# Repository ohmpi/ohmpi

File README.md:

# OhmPi

Development of a low-cost multi-electrodes resistivity meter for electrical resistivity mesaurement for lab applications, based on raspberry board.

Join the community on [Discord](https://discord.gg/2SCKQZBzXh) to share your experience and provide feedback or use the gitlab issue.

## Installation

1. Download a .zip of this repository (or use `git clone https://gitlab.com/ohmpi/ohmpi.git`)
2. Enter the repository (`cd path/to/ohmpi`) and install the software needed. We made a simple script to make it simpler:

`./install.sh`

The installation script will create a virtual python environement `ohmpy` (with a 'y' at the end) where all packages specified in *requirements.txt* will be installed. The script also takes care of creating a configuration for your hardware if you wish.

To activate the environment and set the necessary `$PYTHONPATH` variable, you can use:

`source env.sh`

More examples are provided in the **[documentation](https://ohmpi.gitlab.io/ohmpi/)**.

## Gallery

A few pictures of the components of the OhmPi. More in the [**DOCUMENTATION**](https://ohmpi.gitlab.io/ohmpi/)!

*Measurement board (v2024).*

*Multiplexer board (v2024).*

*Software architecture.*

## How to contribute

You can contribute to the code of OhmPi directly in this repository by raising issue or making merge request. We use different branches to manage different readiness level of the code:
- `issue_XXX` (e.g. `issue_240`) is a branch linked to an issue number to develop a new feature or fix a bug.
- `alpha`: experimental version of the code to be tested by core developers, this branch contains the latest changes but is **unstable**.
- `beta`: **testing** version, more stable than `alpha` that can be tried out by contributors to provide feedback to core developpers (released in winter). 
- `rc`: **release candidate** branch, version to be extensively tested before being released and merged into the `master` branch (released in spring).
- `master`: more **stable** version of the code. Bug fixes can be merged directly to master.

You can also contribute to the **documentation** (on the `docs` branch) by improving the documentation or showcasing your OhmPi application.

## Citing Ohmpi

If you use OhmPi for you work, please cite [this paper](https://www.sciencedirect.com/science/article/pii/S2468067220300316) as:

    Rémi Clement, Yannick Fargier, Vivien Dubois, Julien Gance, Emile Gros, Nicolas Forquet, OhmPi: An open source data logger for 
    dedicated applications of electrical resistivity imaging at the small and laboratory scale, HardwareX, Volume 8, 2020, e00122, ISSN 2468-0672, https://doi.org/10.1016/j.ohx.2020.e00122..

## License information

You may redistribute and modify this documentation and make products using it under the terms of the CERN-OHL-P v2 (https://cern.ch/cern-ohl). This documentation is distributed WITHOUT ANY EXPRESS OR IMPLIED WARRANTY, INCLUDING OF MERCHANTABILITY, SATISFACTORY QUALITY AND FITNESS FOR A PARTICULAR PURPOSE. Please see the CERN-OHL-P v2 for applicable conditions

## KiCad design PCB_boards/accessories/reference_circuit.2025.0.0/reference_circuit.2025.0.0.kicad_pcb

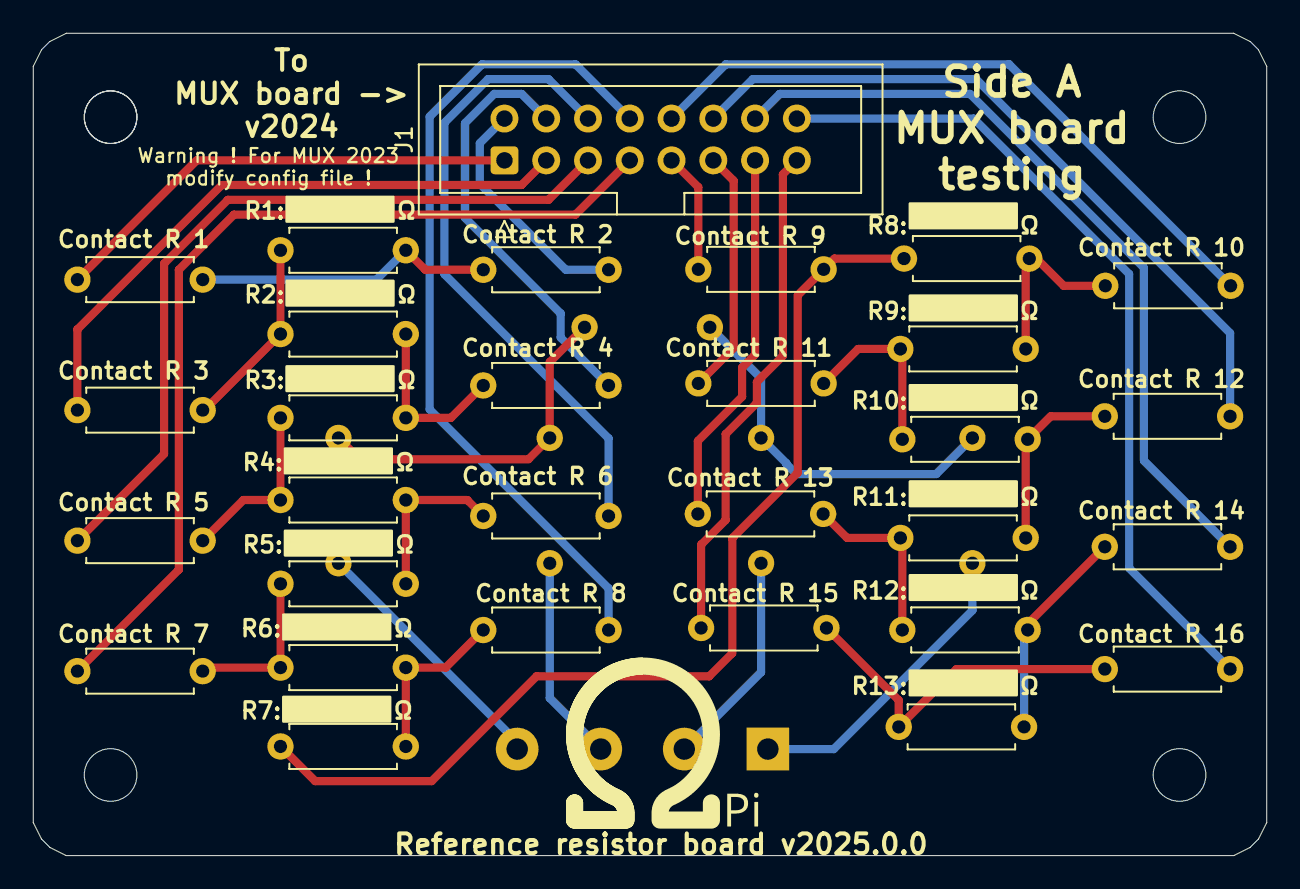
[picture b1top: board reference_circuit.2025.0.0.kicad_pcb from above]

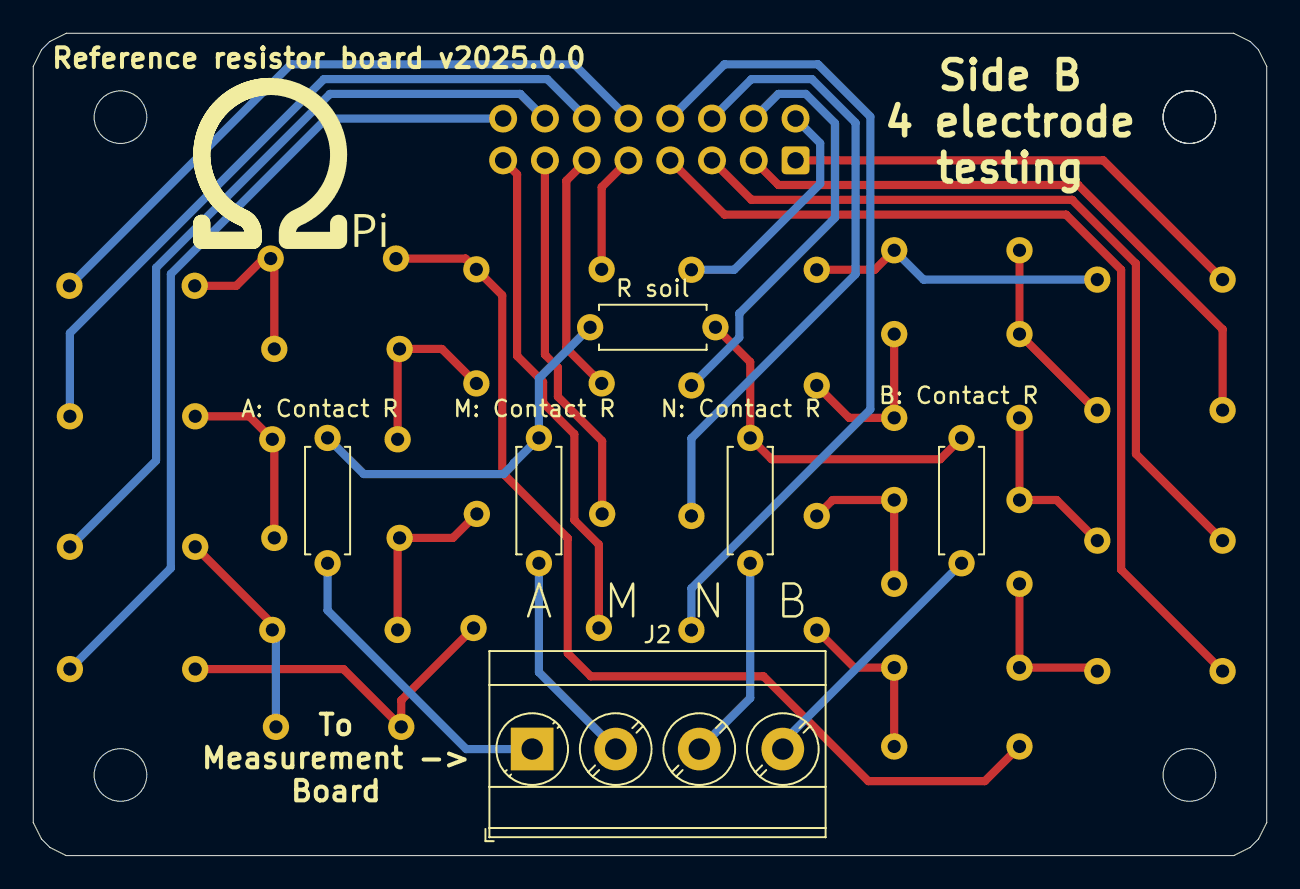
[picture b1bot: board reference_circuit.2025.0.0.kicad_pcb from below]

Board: 2 copper layers, 75.0 x 50.0 mm, 36 parts (6 on the bottom side), 36 nets.

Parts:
A: Contact R: R; R_Axial_DIN0207_L6.3mm_D2.5mm_P7.62mm_Horizontal
B: Contact R: R; R_Axial_DIN0207_L6.3mm_D2.5mm_P7.62mm_Horizontal
J1: Conn_02x08_Odd_Even; IDC-Header_2x08_P2.54mm_Vertical
J2: Screw_Terminal_01x04; TerminalBlock_Phoenix_MKDS-3-4-5.08_1x04_P5.08mm_Horizontal
M: Contact R: R; R_Axial_DIN0207_L6.3mm_D2.5mm_P7.62mm_Horizontal
N: Contact R: R; R_Axial_DIN0207_L6.3mm_D2.5mm_P7.62mm_Horizontal
R1, R2, R3, R4, R5, R6, R7, R8, R9, R10, R11, R12, R13, R14, R15, R16, R18, R19, R20, R21, R22, R23, R24, R25, R26, R27, R28, R29, R30: R; R_Axial_DIN0207_L6.3mm_D2.5mm_P7.62mm_Horizontal
R soil: R; R_Axial_DIN0207_L6.3mm_D2.5mm_P7.62mm_Horizontal

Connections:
unnamed: J1.1, R1.1
unnamed: J1.2, R2.1
unnamed: J1.3, R3.1
unnamed: J1.4, R4.1
unnamed: J1.5, R5.1
unnamed: J1.6, R6.1
unnamed: J1.7, R7.1
unnamed: J1.8, R8.1
unnamed: J1.9, R9.1
unnamed: J1.10, R10.1
unnamed: J1.11, R11.1
unnamed: J1.12, R12.1
unnamed: J1.13, R13.1
unnamed: J1.14, R14.1
unnamed: J1.15, R15.1
unnamed: J1.16, R16.1
unnamed: A: Contact R.1, J2.1
unnamed: J2.2, M: Contact R.1
unnamed: J2.3, N: Contact R.1
unnamed: B: Contact R.1, J2.4
unnamed: R1.2, R2.2, R18.1
unnamed: R10.2, R25.2, R26.1
unnamed: R11.2, R26.2, R27.1
unnamed: R12.2, R27.2, R28.1
unnamed: R13.2, R28.2, R29.1
unnamed: R14.2, R29.2, R30.1
unnamed: R15.2, R16.2, R30.2
unnamed: R3.2, R18.2, R19.1
unnamed: R4.2, R19.2, R20.1
unnamed: R5.2, R20.2, R21.1
unnamed: R6.2, R21.2, R22.1
unnamed: R7.2, R22.2, R23.1
unnamed: R8.2, R23.2, R24.1
unnamed: R9.2, R24.2, R25.1
unnamed: A: Contact R.2, M: Contact R.2, R soil.1
unnamed: B: Contact R.2, N: Contact R.2, R soil.2

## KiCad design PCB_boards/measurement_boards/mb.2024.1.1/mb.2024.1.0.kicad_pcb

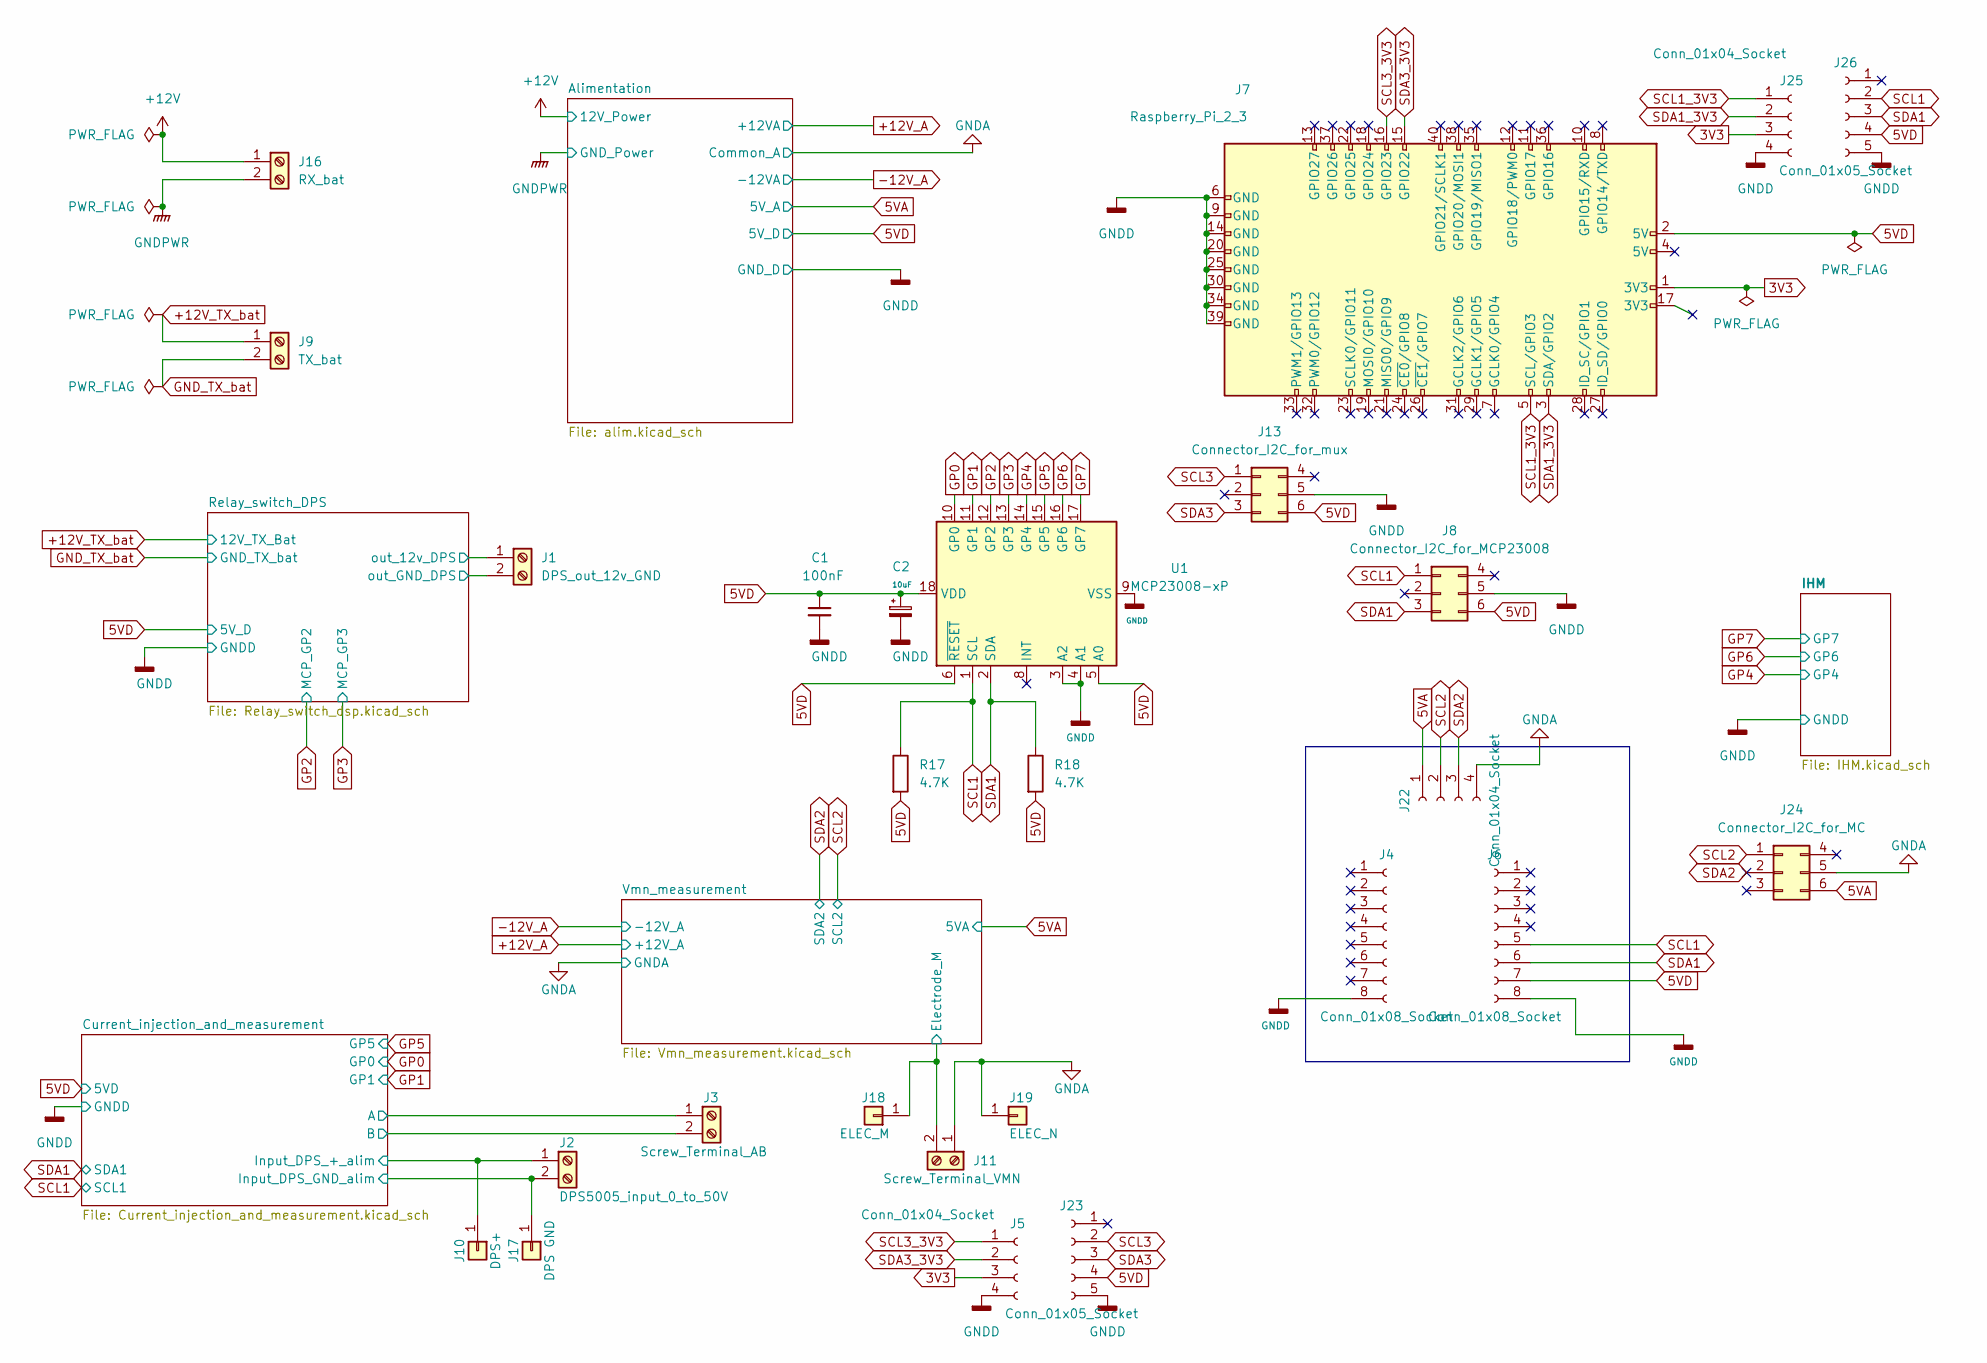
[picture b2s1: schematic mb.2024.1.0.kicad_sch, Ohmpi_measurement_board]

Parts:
C1: 100nF; C_Disc_D8.0mm_W2.5mm_P5.00mm
C2: 10uF; CP_Radial_D6.3mm_P2.50mm
J1: DPS_out_12v_GND; TerminalBlock_Phoenix_MKDS-1,5-2-5.08_1x02_P5.08mm_Horizont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
J2: DPS5005_input_0_to_50V; TerminalBlock_Phoenix_MKDS-1,5-2-5.08_1x02_P5.08mm_Horizont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
J3: Screw_Terminal_AB; TerminalBlock_Phoenix_MKDS-1,5-2-5.08_1x02_P5.08mm_Horizont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
J4, J6: Conn_01x08_Socket; PinHeader_1x08_P2.54mm_Vertical
J5, J22, J25: Conn_01x04_Socket; PinHeader_1x04_P2.54mm_Vertical
J7: Raspberry_Pi_2_3; PinSocket_2x20_P2.54mm_Vertical
J8: Connector_I2C_for_MCP23008; IDC-Header_2x03_P2.54mm_Vertical
J9: TX_bat; TerminalBlock_Phoenix_MKDS-1,5-2-5.08_1x02_P5.08mm_Horizont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
J10: DPS+; PinHeader_1x01_P2.54mm_Vertical
J11: Screw_Terminal_VMN; TerminalBlock_Phoenix_MKDS-1,5-2-5.08_1x02_P5.08mm_Horizont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
J13: Connector_I2C_for_mux; IDC-Header_2x03_P2.54mm_Vertical
J16: RX_bat; TerminalBlock_Phoenix_MKDS-1,5-2-5.08_1x02_P5.08mm_Horizont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
J17: DPS GND; PinHeader_1x01_P2.54mm_Vertical
J18: ELEC_M; PinHeader_1x01_P2.54mm_Vertical
J19: ELEC_N; PinHeader_1x01_P2.54mm_Vertical
J23, J26: Conn_01x05_Socket; PinHeader_1x05_P2.54mm_Vertical
J24: Connector_I2C_for_MC; IDC-Header_2x03_P2.54mm_Vertical
R17, R18: 4.7K; R_Axial_DIN0207_L6.3mm_D2.5mm_P7.62mm_Horizontal
U1: MCP23008-xP; DIP-18_W7.62mm

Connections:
3V3: J5.3, J7.1 (3V3), J25.3
5VA: J22.1, J24.6; also elsewhere on the board
5VD: C1.1, C2.1, J6.7, J7.2 (5V), J8.6, J13.6, J23.4, J26.4, R17.2, R18.2, U1.5 (A0), U1.6 (~RESET), U1.18 (VDD); also elsewhere on the board
+12V: J16.1; also elsewhere on the board
+12V_TX_bat: J9.1; also elsewhere on the board
/Current_injection_and_measurement/A: J3.1; also elsewhere on the board
/Current_injection_and_measurement/B: J3.2; also elsewhere on the board
/Current_injection_and_measurement/Input_DPS_+_alim: J2.1, J10.1; also elsewhere on the board
/Current_injection_and_measurement/Input_DPS_GND_alim: J2.2, J17.1; also elsewhere on the board
/Relay_switch_DPS/out_12v_DPS: J1.1; also elsewhere on the board
/Relay_switch_DPS/out_GND_DPS: J1.2; also elsewhere on the board
/Vmn_measurement/Electrode_M: J11.2, J18.1; also elsewhere on the board
GNDA: J11.1, J19.1, J22.4, J24.5; also elsewhere on the board
GNDD: C1.2, C2.2, J4.8, J5.4, J6.8, J7.6 (GND), J7.9 (GND), J7.14 (GND), J7.20 (GND), J7.25 (GND), J7.30 (GND), J7.34 (GND), J7.39 (GND), J8.5, J13.5, J23.5, J25.4, J26.5, U1.3 (A2), U1.4 (A1), U1.9 (VSS); also elsewhere on the board
GNDPWR: J16.2; also elsewhere on the board
GND_TX_bat: J9.2; also elsewhere on the board
GP0: U1.10 (GP0); also elsewhere on the board
GP1: U1.11 (GP1); also elsewhere on the board
GP2: U1.12 (GP2); also elsewhere on the board
GP3: U1.13 (GP3); also elsewhere on the board
GP4: U1.14 (GP4); also elsewhere on the board
GP5: U1.15 (GP5); also elsewhere on the board
GP6: U1.16 (GP6); also elsewhere on the board
GP7: U1.17 (GP7); also elsewhere on the board
SCL1: J6.5, J8.1, J26.2, R17.1, U1.1 (SCL); also elsewhere on the board
SCL1_3V3: J7.5 (SCL/GPIO3), J25.1
SCL2: J22.2, J24.1; also elsewhere on the board
SCL3: J13.1, J23.2
SCL3_3V3: J5.1, J7.16 (GPIO23)
SDA1: J6.6, J8.3, J26.3, R18.1, U1.2 (SDA); also elsewhere on the board
SDA1_3V3: J7.3 (SDA/GPIO2), J25.2
SDA2: J22.3, J24.2; also elsewhere on the board
SDA3: J13.3, J23.3
SDA3_3V3: J5.2, J7.15 (GPIO22)

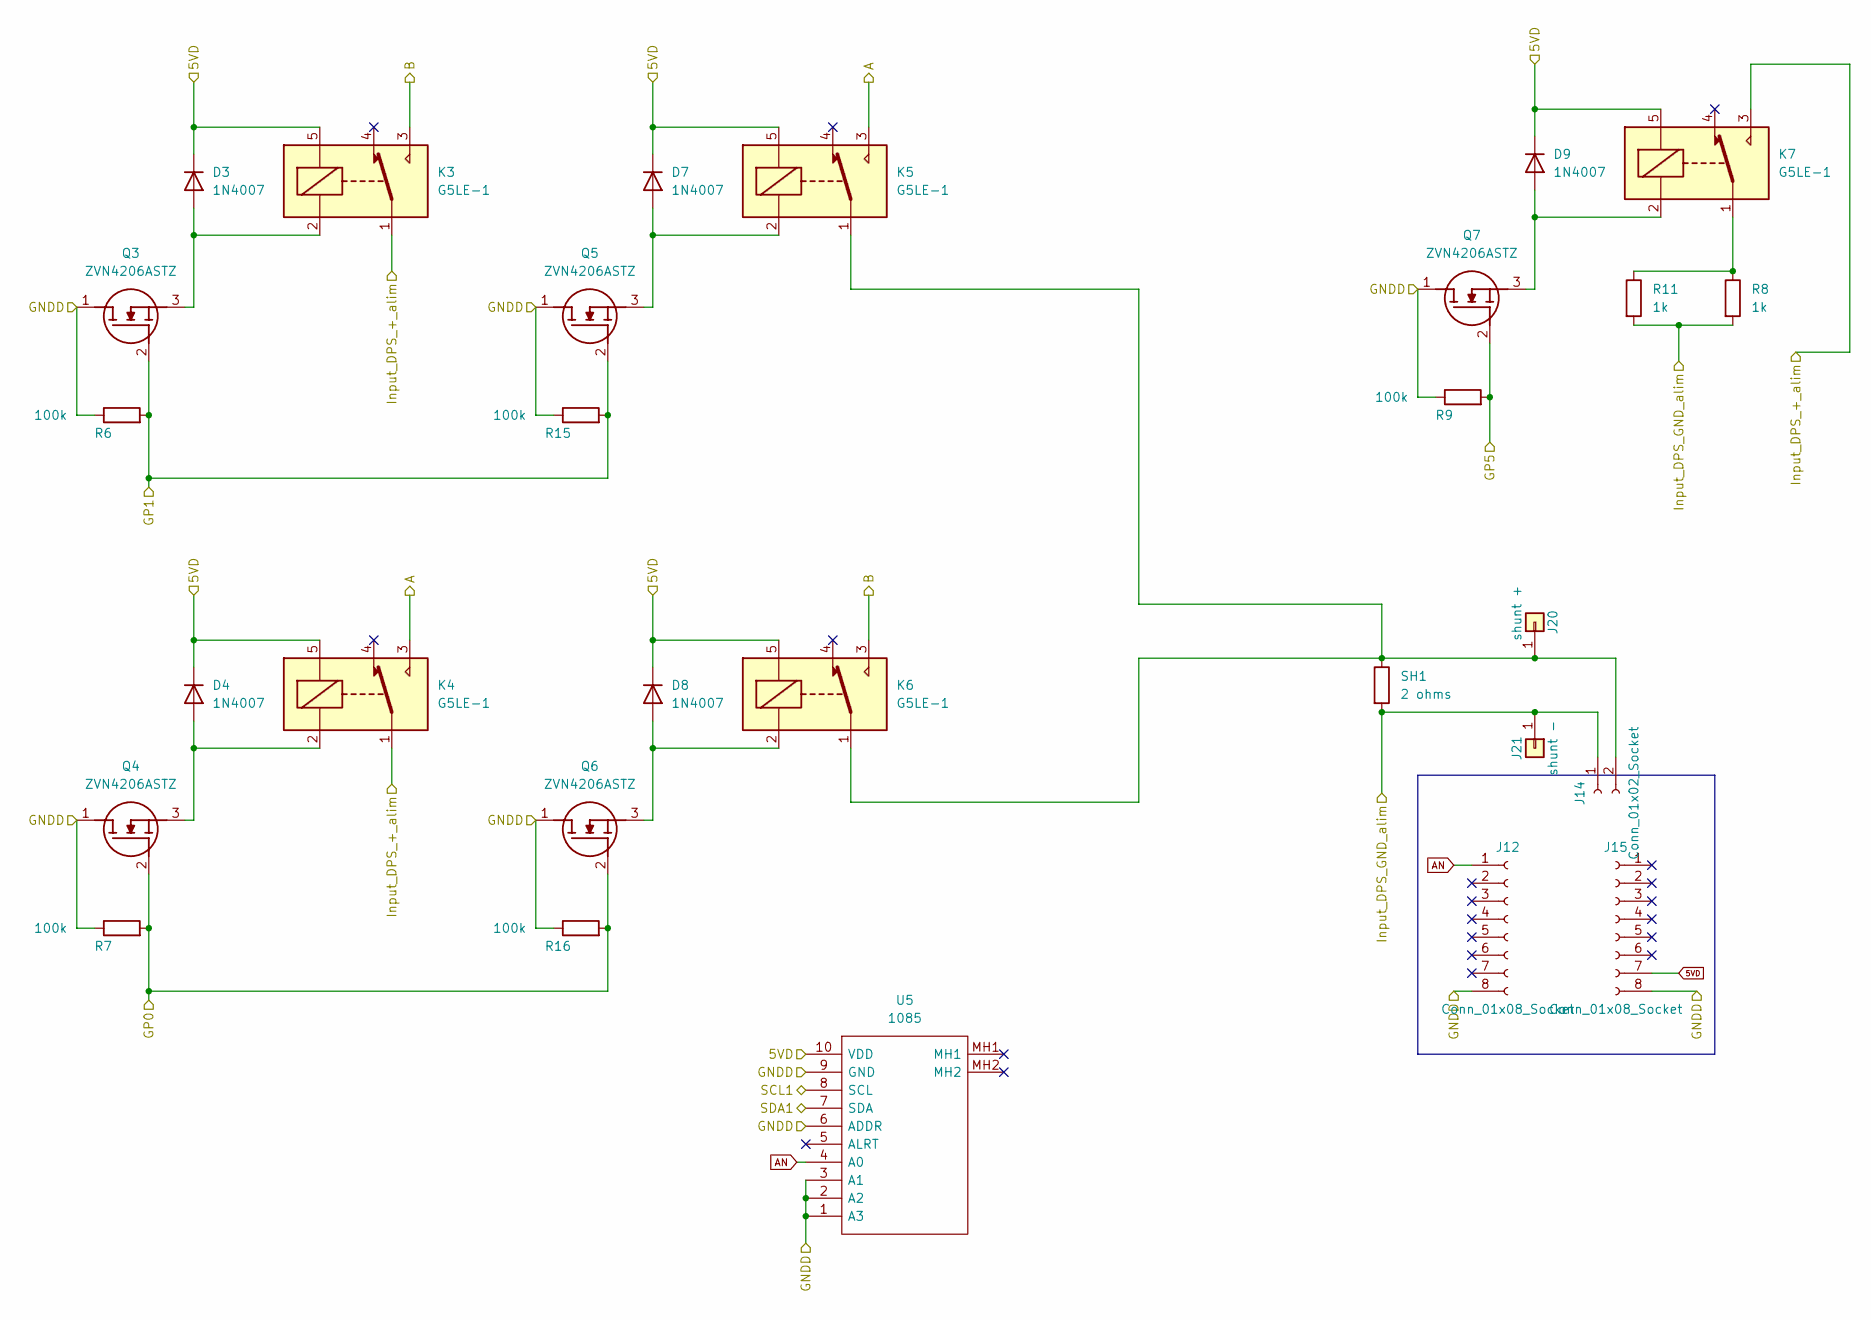
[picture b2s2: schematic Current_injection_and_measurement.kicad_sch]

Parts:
D3, D4, D7, D8, D9: 1N4007; D_DO-41_SOD81_P10.16mm_Horizontal
J12, J15: Conn_01x08_Socket; PinHeader_1x08_P2.54mm_Vertical
J14: Conn_01x02_Socket; PinHeader_1x02_P2.54mm_Vertical
J20: shunt +; PinHeader_1x01_P2.54mm_Vertical
J21: shunt -; PinHeader_1x01_P2.54mm_Vertical
K3, K4, K5, K6, K7: G5LE-1; Relay_SPDT_Omron-G5LE-1
Q3, Q4, Q5, Q6, Q7: ZVN4206ASTZ; TO-92L_Wide; Manufacturer_Part_Number ZVN4206ASTZ; Mouser Part Number 522-ZVN4206ASTZ
R6, R7, R9, R15, R16: 100k; R_Axial_DIN0207_L6.3mm_D2.5mm_P7.62mm_Horizontal
R8, R11: 1k; R_Axial_DIN0207_L6.3mm_D2.5mm_P7.62mm_Horizontal
SH1: 2 ohms; R_Axial_DIN0414_L11.9mm_D4.5mm_P20.32mm_Horizontal
U5: 1085; Manufacturer_Part_Number 1085; Mouser Part Number 485-1085

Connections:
5VD: D3.1 (K), D4.1 (K), D7.1 (K), D8.1 (K), D9.1 (K), J15.7, K3.5, K4.5, K5.5, K6.5, K7.5, U5.10 (VDD); also elsewhere on the board
/Current_injection_and_measurement/A: K4.3, K5.3; also elsewhere on the board
/Current_injection_and_measurement/B: K3.3, K6.3; also elsewhere on the board
/Current_injection_and_measurement/Input_DPS_+_alim: K3.1, K4.1, K7.3; also elsewhere on the board
/Current_injection_and_measurement/Input_DPS_GND_alim: J14.1, J21.1, R8.2, R11.2, SH1.2; also elsewhere on the board
AN: J12.1, U5.4 (A0)
GNDD: J12.8, J15.8, Q3.1 (D), Q4.1 (D), Q5.1 (D), Q6.1 (D), Q7.1 (D), R6.1, R7.1, R9.1, R15.1, R16.1, U5.1 (A3), U5.2 (A2), U5.3 (A1), U5.6 (ADDR), U5.9 (GND); also elsewhere on the board
GP0: Q4.2 (G), Q6.2 (G), R7.2, R16.2; also elsewhere on the board
GP1: Q3.2 (G), Q5.2 (G), R6.2, R15.2; also elsewhere on the board
GP5: Q7.2 (G), R9.2; also elsewhere on the board
unnamed: D3.2 (A), K3.2, Q3.3 (S)
unnamed: D4.2 (A), K4.2, Q4.3 (S)
unnamed: D7.2 (A), K5.2, Q5.3 (S)
unnamed: D8.2 (A), K6.2, Q6.3 (S)
unnamed: D9.2 (A), K7.2, Q7.3 (S)
unnamed: J14.2, J20.1, K5.1, K6.1, SH1.1
unnamed: K7.1, R8.1, R11.1
SCL1: U5.8 (SCL); also elsewhere on the board
SDA1: U5.7 (SDA); also elsewhere on the board

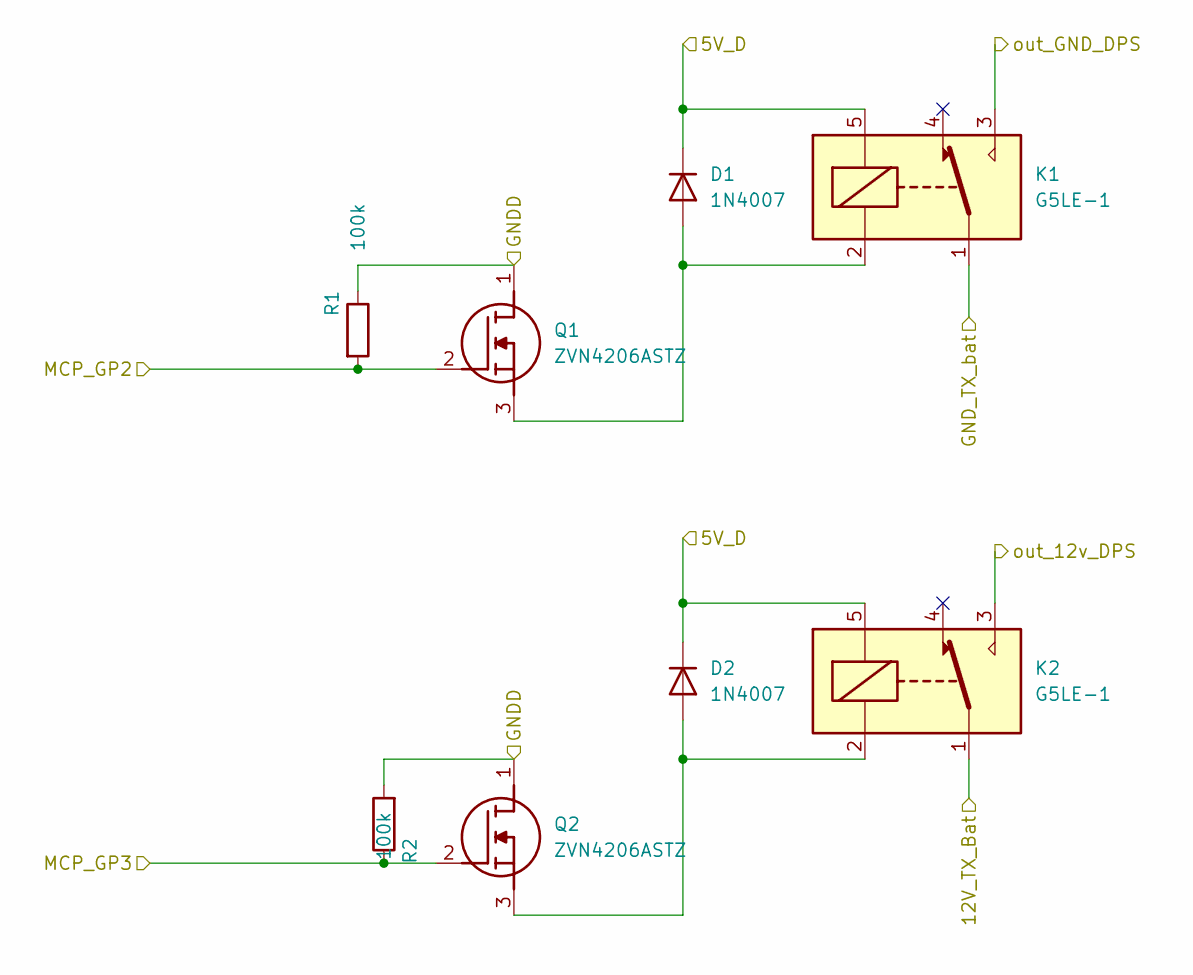
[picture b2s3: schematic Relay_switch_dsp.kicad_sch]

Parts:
D1, D2: 1N4007; D_DO-41_SOD81_P10.16mm_Horizontal
K1, K2: G5LE-1; Relay_SPDT_Omron-G5LE-1
Q1, Q2: ZVN4206ASTZ; TO-92L_Wide; Manufacturer_Part_Number ZVN4206ASTZ; Mouser Part Number 522-ZVN4206ASTZ
R1, R2: 100k; R_Axial_DIN0207_L6.3mm_D2.5mm_P7.62mm_Horizontal

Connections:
5VD: D1.1 (K), D2.1 (K), K1.5, K2.5; also elsewhere on the board
+12V_TX_bat: K2.1; also elsewhere on the board
/Relay_switch_DPS/out_12v_DPS: K2.3; also elsewhere on the board
/Relay_switch_DPS/out_GND_DPS: K1.3; also elsewhere on the board
GNDD: Q1.1 (D), Q2.1 (D), R1.1, R2.2; also elsewhere on the board
GND_TX_bat: K1.1; also elsewhere on the board
GP2: Q1.2 (G), R1.2; also elsewhere on the board
GP3: Q2.2 (G), R2.1; also elsewhere on the board
unnamed: D1.2 (A), K1.2, Q1.3 (S)
unnamed: D2.2 (A), K2.2, Q2.3 (S)

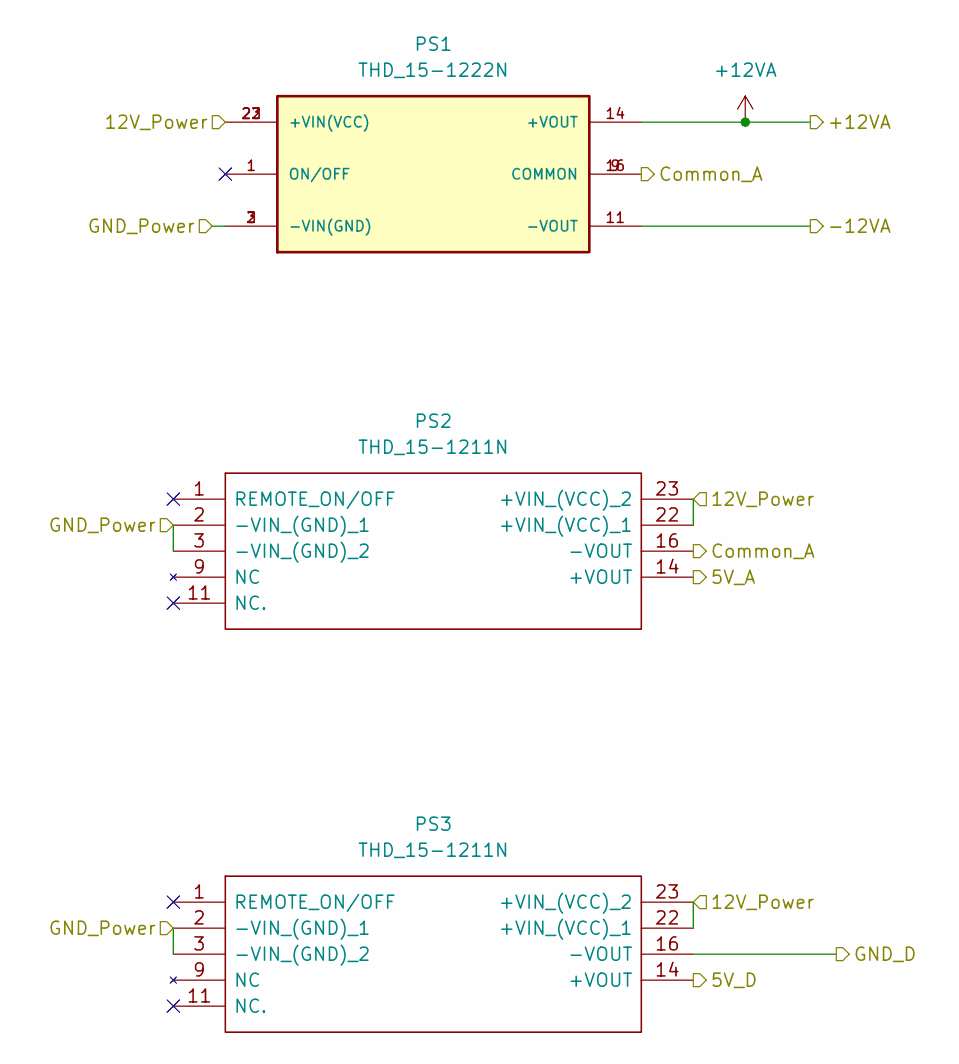
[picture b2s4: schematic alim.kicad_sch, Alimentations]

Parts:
PS1: THD_15-1222N; CONV_THD_15-1222N; PARTREV July 27, 2020
PS2, PS3: THD_15-1211N; THD151211N; Manufacturer_Part_Number THD 15-1211N; Mouser Part Number 495-THD15-1211N

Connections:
5VA: PS2.14 (+VOUT); also elsewhere on the board
5VD: PS3.14 (+VOUT); also elsewhere on the board
+12V: PS1.22 (+VIN(VCC)), PS1.23 (+VIN(VCC)), PS2.22 (+VIN_(VCC)_1), PS2.23 (+VIN_(VCC)_2), PS3.22 (+VIN_(VCC)_1), PS3.23 (+VIN_(VCC)_2); also elsewhere on the board
+12V_A: PS1.14 (+VOUT); also elsewhere on the board
-12V_A: PS1.11 (-VOUT); also elsewhere on the board
GNDA: PS1.9 (COMMON), PS1.16 (COMMON), PS2.16 (-VOUT); also elsewhere on the board
GNDD: PS3.16 (-VOUT); also elsewhere on the board
GNDPWR: PS1.2 (-VIN(GND)), PS1.3 (-VIN(GND)), PS2.2 (-VIN_(GND)_1), PS2.3 (-VIN_(GND)_2), PS3.2 (-VIN_(GND)_1), PS3.3 (-VIN_(GND)_2); also elsewhere on the board

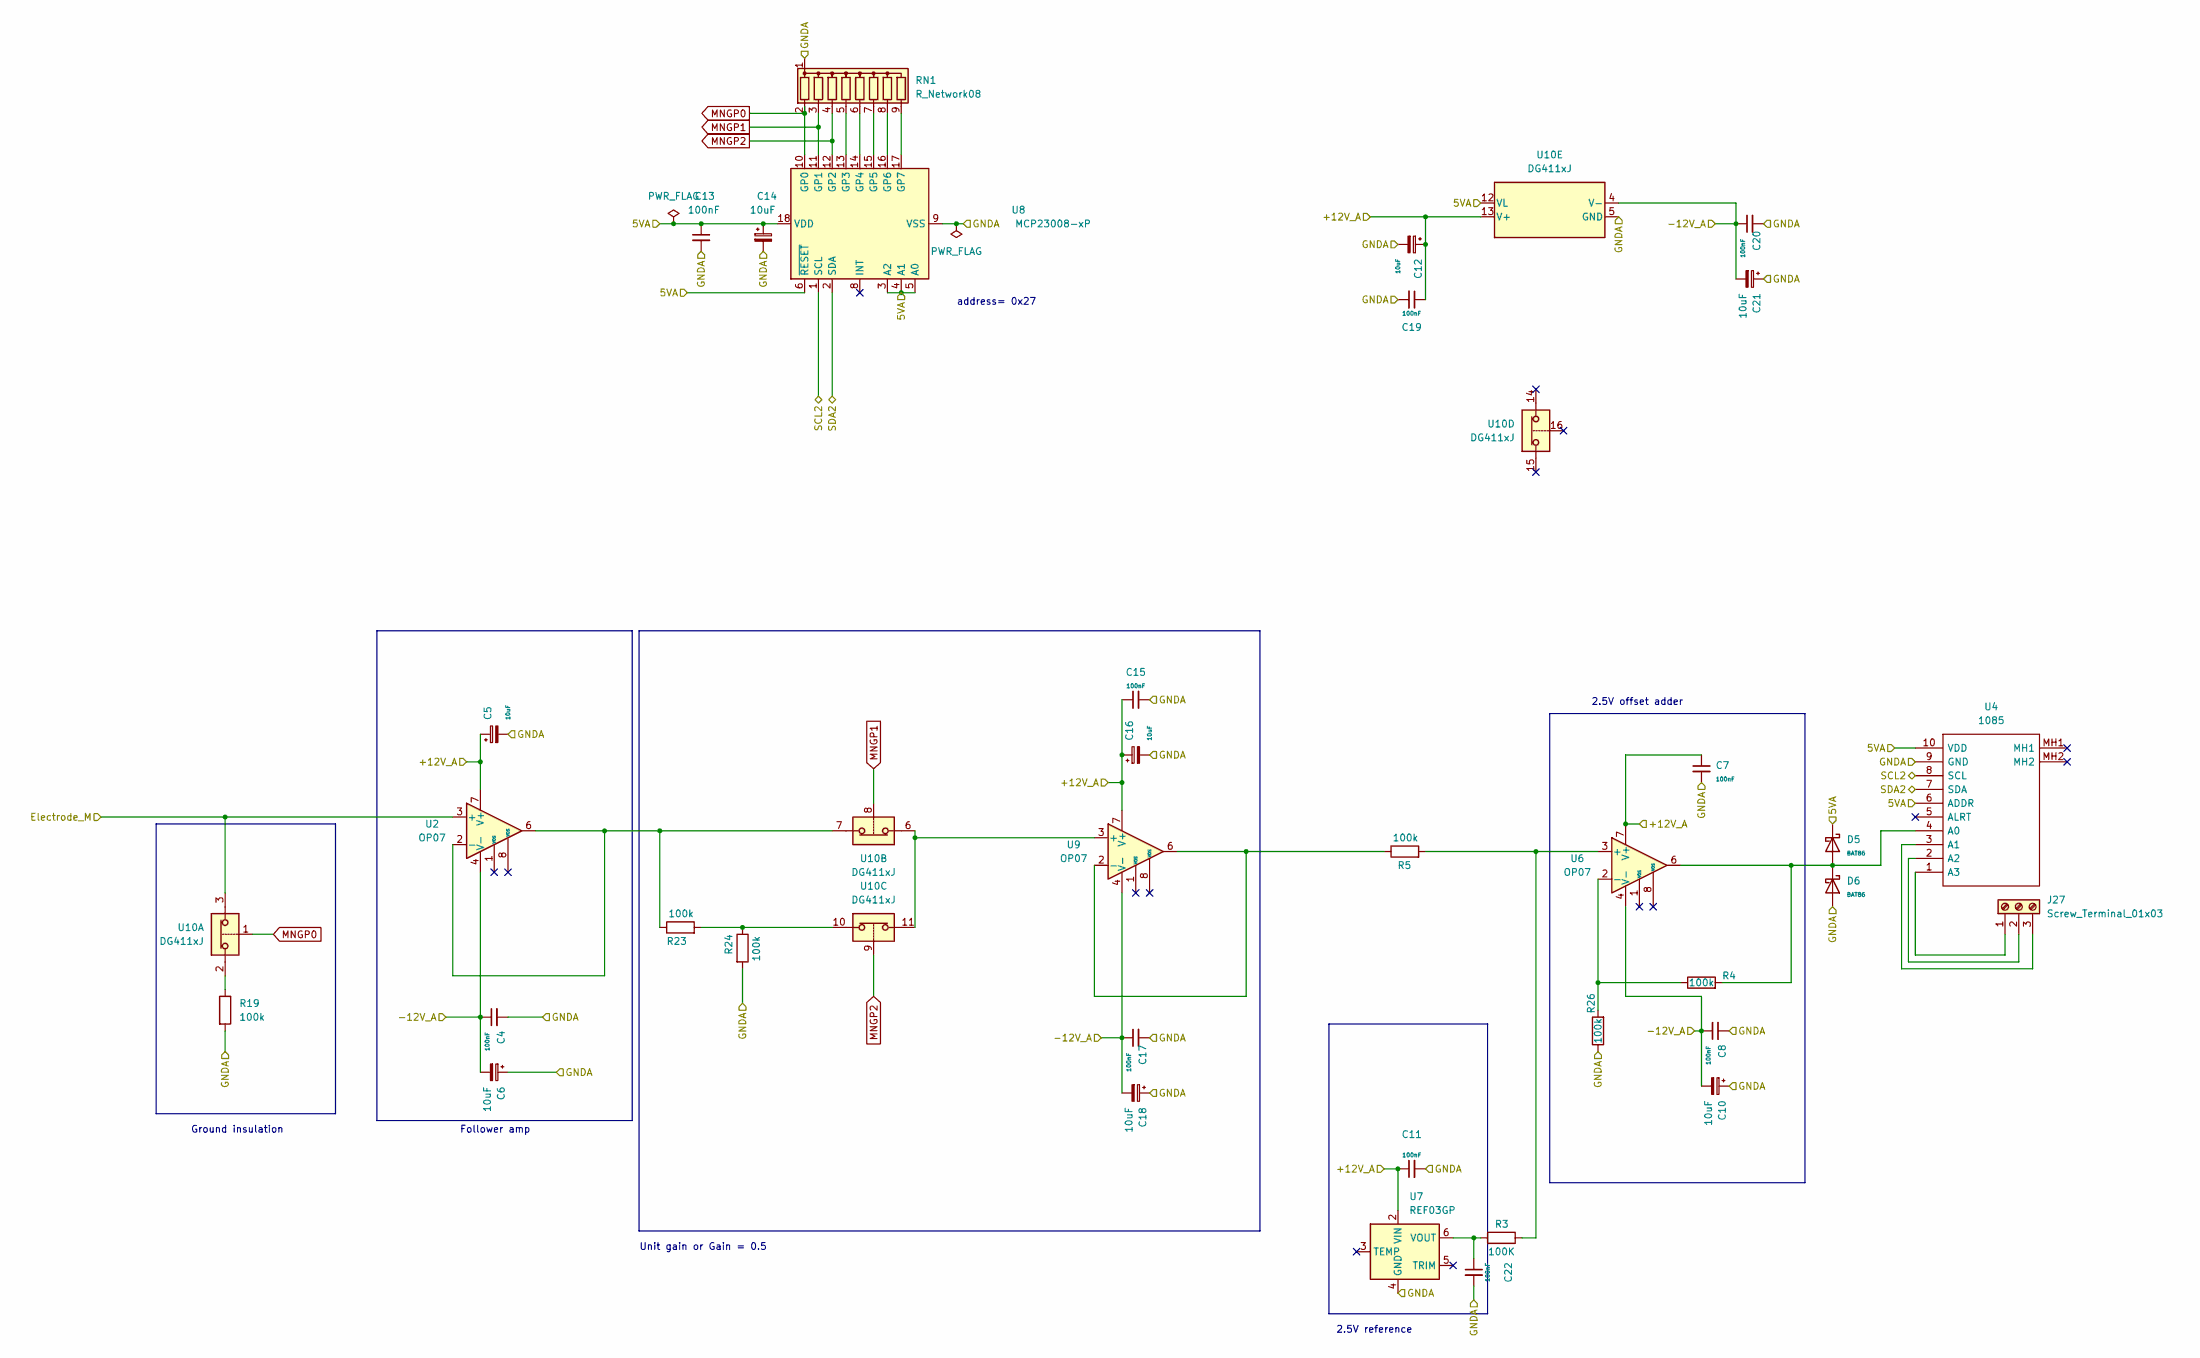
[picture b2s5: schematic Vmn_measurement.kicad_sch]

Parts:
C4, C7, C8, C11, C13, C15, C17, C19, C20, C22: 100nF; C_Disc_D8.0mm_W2.5mm_P5.00mm
C5, C6, C10, C12, C14, C16, C18, C21: 10uF; CP_Radial_D6.3mm_P2.50mm
D5, D6: BAT86; D_DO-35_SOD27_P7.62mm_Horizontal
J27: Screw_Terminal_01x03; TerminalBlock_bornier-3_P5.08mm
R3: 100K; R_Axial_DIN0207_L6.3mm_D2.5mm_P7.62mm_Horizontal
R4, R5, R19, R23, R24, R26: 100k; R_Axial_DIN0207_L6.3mm_D2.5mm_P7.62mm_Horizontal
RN1: R_Network08; R_Array_SIP9
U2, U6, U9: OP07; DIP-8_W7.62mm
U4: 1085; Manufacturer_Part_Number 1085; Mouser Part Number 485-1085
U7: REF03GP; DIP-8_W7.62mm
U8: MCP23008-xP; DIP-18_W7.62mm
U10: DG411xJ; DIP-16_W7.62mm

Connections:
5VA: C13.1, C14.1, D5.1 (K), U4.6 (ADDR), U4.10 (VDD), U8.3 (A2), U8.4 (A1), U8.5 (A0), U8.6 (~RESET), U8.18 (VDD), U10.12 (VL); also elsewhere on the board
+12V_A: C5.1, C7.1, C11.1, C12.1, C15.1, C16.1, C19.1, U2.7 (V+), U6.7 (V+), U7.2 (VIN), U9.7 (V+), U10.13 (V+); also elsewhere on the board
-12V_A: C4.1, C6.2, C8.1, C10.2, C17.1, C18.2, C20.1, C21.2, U2.4 (V-), U6.4 (V-), U9.4 (V-), U10.4 (V-); also elsewhere on the board
/Vmn_measurement/Electrode_M: U2.3 (+), U10.3; also elsewhere on the board
GNDA: C4.2, C5.2, C6.1, C7.2, C8.2, C10.1, C11.2, C12.2, C13.2, C14.2, C15.2, C16.2, C17.2, C18.1, C19.2, C20.2, C21.1, C22.2, D6.2 (A), R19.2, R24.2, R26.1, RN1.1 (common), U4.9 (GND), U7.4 (GND), U8.9 (VSS), U10.5 (GND); also elsewhere on the board
MNGP0: RN1.2 (R1), U8.10 (GP0), U10.1
MNGP1: RN1.3 (R2), U8.11 (GP1), U10.8
MNGP2: RN1.4 (R3), U8.12 (GP2), U10.9
unnamed: D5.2 (A), D6.1 (K), R4.2, U4.4 (A0), U6.6
unnamed: J27.1, U4.1 (A3)
unnamed: J27.2, U4.2 (A2)
unnamed: J27.3, U4.3 (A1)
unnamed: R19.1, U10.2
unnamed: R23.2, R24.1, U10.10
unnamed: RN1.5 (R4), U8.13 (GP3)
unnamed: RN1.6 (R5), U8.14 (GP4)
unnamed: RN1.7 (R6), U8.15 (GP5)
unnamed: RN1.8 (R7), U8.16 (GP6)
unnamed: RN1.9 (R8), U8.17 (GP7)
unnamed: R23.1, U2.2 (-), U2.6, U10.7
unnamed: R3.1, R5.2, U6.3 (+)
unnamed: R4.1, R26.2, U6.2 (-)
unnamed: C22.1, R3.2, U7.6 (VOUT)
unnamed: U9.3 (+), U10.6, U10.11
unnamed: R5.1, U9.2 (-), U9.6
SCL2: U4.8 (SCL), U8.1 (SCL); also elsewhere on the board
SDA2: U4.7 (SDA), U8.2 (SDA); also elsewhere on the board

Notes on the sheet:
Follower amp
address= 0x27
Ground insulation
2.5V reference
Unit gain or Gain = 0.5
2.5V offset adder

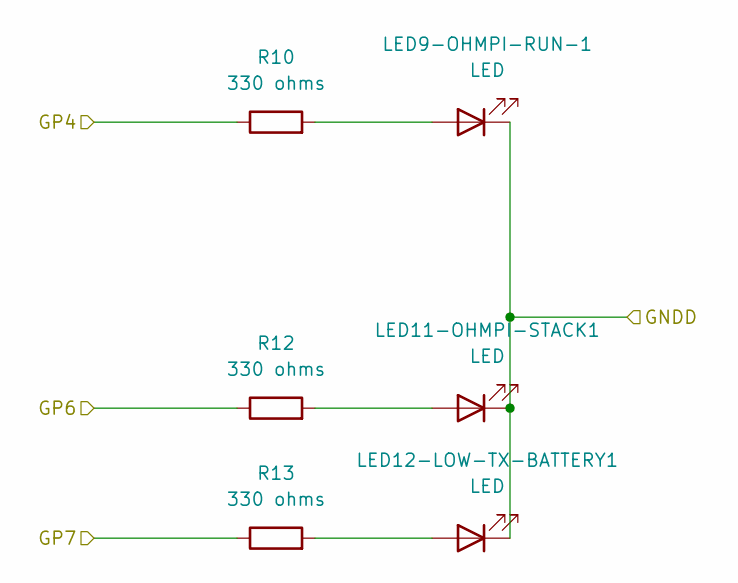
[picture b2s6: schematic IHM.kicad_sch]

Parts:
LED9-OHMPI-RUN-1, LED11-OHMPI-STACK1, LED12-LOW-TX-BATTERY1: LED; LED_D4.0mm
R10, R12, R13: 330 ohms; R_Axial_DIN0207_L6.3mm_D2.5mm_P7.62mm_Horizontal

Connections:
GNDD: LED9-OHMPI-RUN-1.1 (K), LED11-OHMPI-STACK1.1 (K), LED12-LOW-TX-BATTERY1.1 (K); also elsewhere on the board
GP4: R10.1; also elsewhere on the board
GP6: R12.1; also elsewhere on the board
GP7: R13.1; also elsewhere on the board
unnamed: LED9-OHMPI-RUN-1.2 (A), R10.2
unnamed: LED11-OHMPI-STACK1.2 (A), R12.2
unnamed: LED12-LOW-TX-BATTERY1.2 (A), R13.2

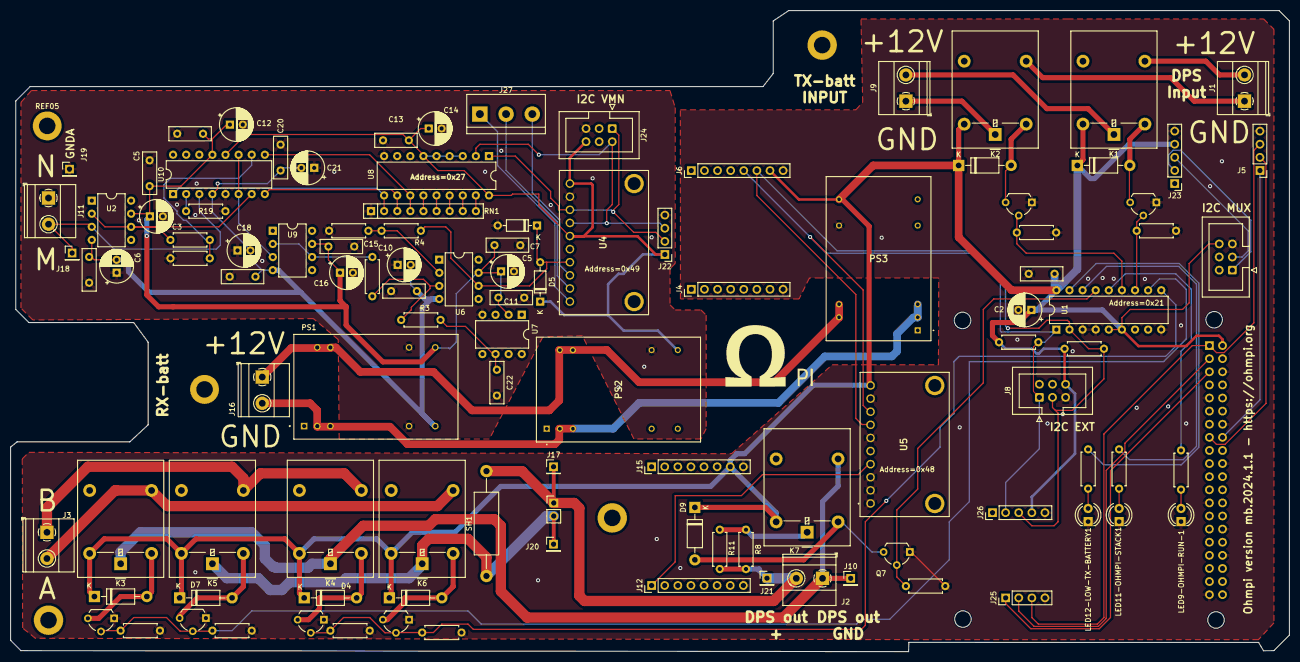
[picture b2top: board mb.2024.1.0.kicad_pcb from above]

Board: 2 copper layers, 247.8 x 124.2 mm, 116 parts (1 on the bottom side), 69 nets.

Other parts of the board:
C3, C5#2: 10uF; CP_Radial_D6.3mm_P2.50mm
REF00, REF01, REF2, REF03: MountingHole_3.2mm_M3
REF04, REF05: MountingHole_3.2mm_M3_DIN965_Pad

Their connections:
+12V_A: C3.1, C5#2.1; also elsewhere on the board
GNDA: C3.2, C5#2.2; also elsewhere on the board
